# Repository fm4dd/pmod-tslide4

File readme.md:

## TSLIDE4 PMOD

### Description

This PMOD provides four slide switch and four touch-button inputs to FPGA designs via a single double-row PMOD. The four slide switches can be individually disabled through two sets of jumpers (J2 and J3, signal S1-S4). This can free up IO pins on the IceBreaker v1.0 board if only push-buttons are needed. The Icebreaker has only 24 multi-purpose IO, which creates a challenge for advanced designs. Push buttons use inverse logic, the button press creates a "LOW" signal.

http://fpga.fm4dd.com/

### Schematic

### PCB Gerber

[20200301 TSLIDE4 Gerber v1.1](20200301-tslide4-gerber-v11.zip)

### Pin Assignments

#### IceBreaker v1.0

TSLIDE4 PMOD, connected to a Icebreaker v1.0 board

 J1# |  Label | Description   | PMOD1A| PMOD1B | PMOD2
-----|--------|---------------|-------|--------|-------
1    |  SW1   | Slide Switch1 | 4     | 43     | 27
2    |  SW2   | Slide Switch2 | 2     | 38     | 25
3    |  SW3   | Slide Switch3 | 47    | 34     | 21
4    |  SW4   | Slide Switch4 | 45    | 31     | 19
7    |  PB1   | Push Button1  | 3     | 42     | 26
8    |  PB2   | Push Button2  | 48    | 36     | 23
9    |  PB3   | Push Button3  | 46    | 32     | 20
10   |  PB4   | Push Button4  | 44    | 28     | 18

#### DE0-Nano-SoC

The connection to Intels DE0-Nano-SoC is made through the pmod2nano adapter.

 J1# |  Label | Description   | GPIO0A | GPIO0B | GPIO1A | GPIO1B
-----|--------|---------------|--------|--------|--------|--------
1    |  PB1   | Push Button1  | PIN_W12| PIN_AF4|PIN_AA15| PIN_AH23
2    |  PB2   | Push Button2  | PIN_Y8 | PIN_AF5|PIN_AG26| PIN_AE19
3    |  PB3   | Push Button3  | PIN_W8 | PIN_T13|PIN_AF23| PIN_AD19
4    |  PB4   | Push Button4  | PIN_Y5 | PIN_AE7|PIN_AF21| PIN_AE24
7    |  SW1   | Slide Switch1 | PIN_AF8| PIN_AG6|PIN_AH27| PIN_AG23
8    |  SW2   | Slide Switch2 | PIN_AB4| PIN_AE4|PIN_AH24| PIN_AF18
9    |  SW3   | Slide Switch3 | PIN_Y4 | PIN_T11|PIN_AE22| PIN_AE20
10   |  SW4   | Slide Switch4 | PIN_U11| PIN_AF6|PIN_AG20| PIN_AD20

### Example Code

#### Verilog

Below is a test program to verify the correct function of the TSLIDE4 PMOD.
The programm assumes an additional 8LED2 PMOD connected to show LED output.

The design links the four slide switches with LED D1-D4 in green color,
and the four push button switches with LED D5-D8 in red color.

Operating the switches simply turns the corresponding LED on or off.

Verilog test program pmod_tslide4_1.v (top-level):
```
// -------------------------------------------------------
// This program tests HW pin assignment for TSlide4 pmods
// -------------------------------------------------------
module pmod_tslide4_1 (
  input SW1,
  input SW2,
  input SW3,
  input SW4,
  input PB1,
  input PB2,
  input PB3,
  input PB4,
  output reg [0:7] pmodledg,
  output reg [0:7] pmodledr
);

always
begin
  // pmodledg[0] = 1'b1;  // light up D1
  pmodledg[0] = SW1;
  pmodledg[1] = SW2;
  pmodledg[2] = SW3;
  pmodledg[3] = SW4;
  pmodledr[7] = ~PB1;
  pmodledr[6] = ~PB2;
  pmodledr[5] = ~PB3;
  pmodledr[4] = ~PB4;
end
endmodule
```
#### VHDL

This is Verilog test program pmod_tslide4_1.v converted to VHDL as pmod_tslide4_2.vhd

```
-- -------------------------------------------------------
-- This program tests HW pin assignment for TSlide4 pmods
-- -------------------------------------------------------
library ieee;
use ieee.std_logic_1164.all;
use ieee.numeric_std.all;

entity pmod_tslide4_2 is
port ( SW1: in STD_LOGIC := '1';
       SW2: in STD_LOGIC := '1';
       SW3: in STD_LOGIC := '1';
       SW4: in STD_LOGIC := '1';
       PB1: in STD_LOGIC := '1';
       PB2: in STD_LOGIC := '1';
       PB3: in STD_LOGIC := '1';
       PB4: in STD_LOGIC := '1';
  pmodledg: out STD_LOGIC_VECTOR(0 to 7) := "00000000";
  pmodledr: out STD_LOGIC_VECTOR(0 to 7) := "00000000"
);
end pmod_tslide4_2;

architecture arch of pmod_tslide4_2 is
begin
  -- pmodledg(0) <= '1';  // light up D1
  pmodledg(0) <= SW1;
  pmodledg(1) <= SW2;
  pmodledg(2) <= SW3;
  pmodledg(3) <= SW4;

  pmodledr(4) <= NOT PB1;
  pmodledr(5) <= NOT PB2;
  pmodledr(6) <= NOT PB3;
  pmodledr(7) <= NOT PB4;
end arch;
```

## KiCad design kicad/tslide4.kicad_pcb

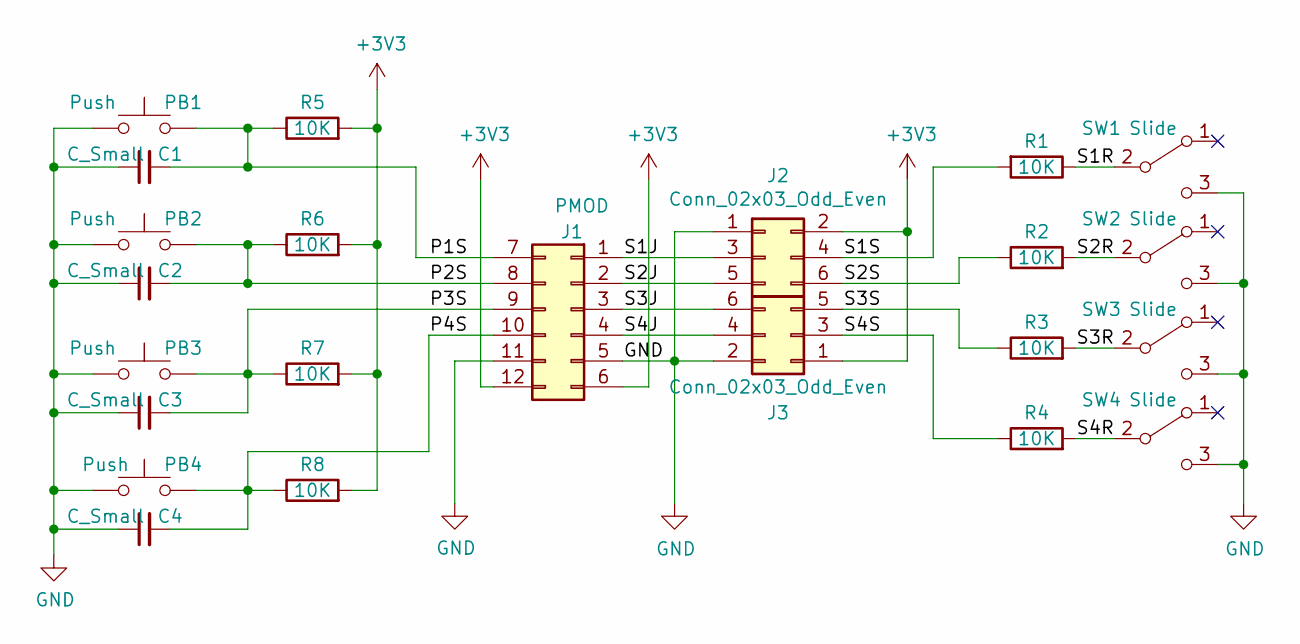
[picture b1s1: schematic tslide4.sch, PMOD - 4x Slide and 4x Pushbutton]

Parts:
C1, C2, C3, C4: C_Small; C_Disc_D3.0mm_W1.6mm_P2.50mm
J1: PMOD; PMODHeader_2x06_P2.54mm_Horizontal
J2, J3: Conn_02x03_Odd_Even; PinHeader_2x03_P2.54mm_Vertical
PB1, PB2, PB3, PB4: Push; SW_PUSH_6mm
R1, R2, R3, R4, R5, R6, R7, R8: 10K; R_Axial_DIN0204_L3.6mm_D1.6mm_P5.08mm_Horizontal
SW1, SW2, SW3, SW4: Slide; SlideSW_SS12-D01

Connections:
+3V3: J1.6, J1.12, J2.2, J3.1, R5.2, R6.2, R7.2, R8.2
/P1S: C1.2, J1.7, PB1.2, R5.1
/P2S: C2.2, J1.8, PB2.2, R6.1
/P3S: C3.2, J1.9, PB3.2, R7.1
/P4S: C4.2, J1.10, PB4.2, R8.1
/S1J: J1.1, J2.3
/S1R: R1.1, SW1.2 (B)
/S1S: J2.4, R1.2
/S2J: J1.2, J2.5
/S2R: R2.2, SW2.2 (B)
/S2S: J2.6, R2.1
/S3J: J1.3, J3.6
/S3R: R3.2, SW3.2 (B)
/S3S: J3.5, R3.1
/S4J: J1.4, J3.4
/S4R: R4.2, SW4.2 (B)
/S4S: J3.3, R4.1
GND: C1.1, C2.1, C3.1, C4.1, J1.5, J1.11, J2.1, J3.2, PB1.1, PB2.1, PB3.1, PB4.1, SW1.3 (C), SW2.3 (C), SW3.3 (C), SW4.3 (C)

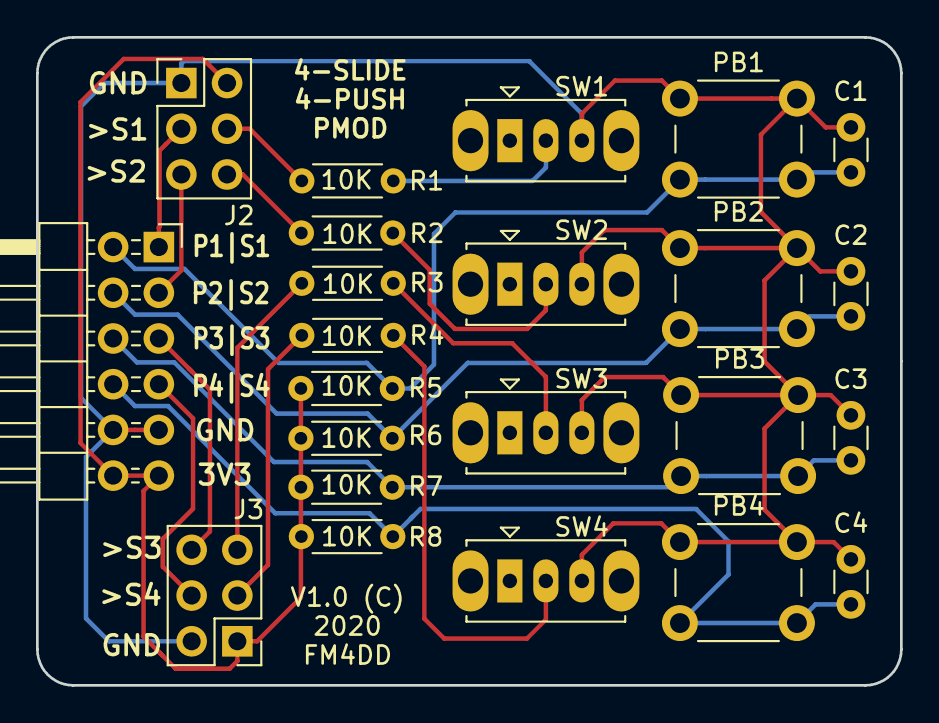
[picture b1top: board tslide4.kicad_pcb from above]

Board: 2 copper layers, 48.0 x 36.0 mm, 23 parts (0 on the bottom side), 18 nets.

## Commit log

2020-03-20 add fpga url
2020-04-04 add BOM
2020-04-05 add VHDL example
2020-04-19 add Verilog/VHDL demo code
2020-04-23 fix git lang discovery
2020-12-03 add VHDL examples

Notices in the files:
kicad/tslide4.kicad_pcb:
License: CC-BY-SA 4.0
CC-BY-SA
